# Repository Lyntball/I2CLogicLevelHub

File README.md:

# I2CLogicLevelHub
I2C Logic Level Hub for Sensor Reading and Device Control

This is a Logic Level Hub for Reading Sensors or controlling devices. Using the RJ-45 connections and normal network cabling devices can reach distances over 100 feet using onle I2C to communicate.

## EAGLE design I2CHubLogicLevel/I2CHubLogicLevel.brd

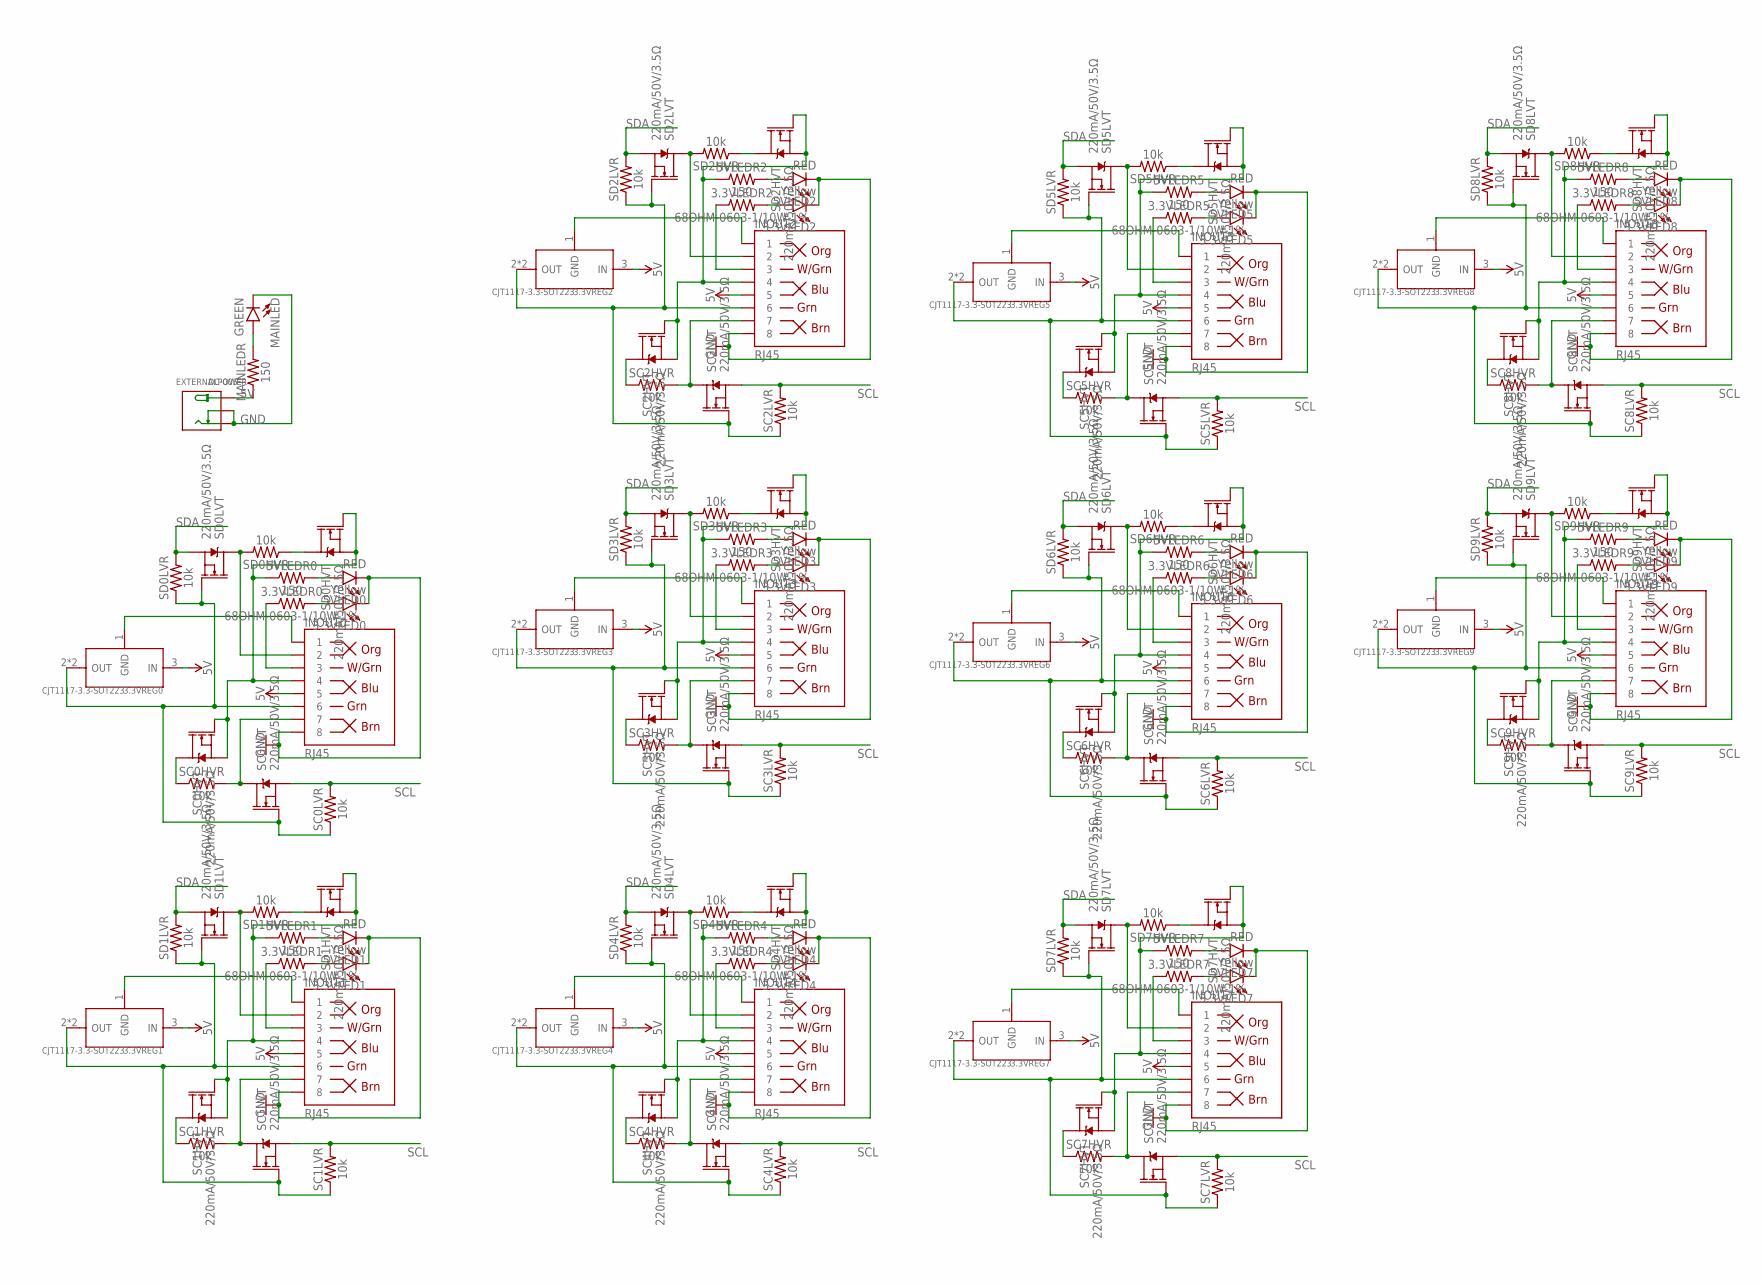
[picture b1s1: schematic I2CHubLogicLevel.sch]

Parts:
3.3VLED0, 3.3VLED1, 3.3VLED2, 3.3VLED3, 3.3VLED4, 3.3VLED5, 3.3VLED6, 3.3VLED7, 3.3VLED8, 3.3VLED9: Yellow; LED-0603
3.3VLEDR0, 3.3VLEDR1, 3.3VLEDR2, 3.3VLEDR3, 3.3VLEDR4, 3.3VLEDR5, 3.3VLEDR6, 3.3VLEDR7, 3.3VLEDR8, 3.3VLEDR9: 68OHM-0603-1/10W-1%; 0603
3.3VREG0, 3.3VREG1, 3.3VREG2, 3.3VREG3, 3.3VREG4, 3.3VREG5, 3.3VREG6, 3.3VREG7, 3.3VREG8, 3.3VREG9: CJT1117-3.3-SOT223; SOT-223
5VLED0, 5VLED1, 5VLED2, 5VLED3, 5VLED4, 5VLED5, 5VLED6, 5VLED7, 5VLED8, 5VLED9: RED; LED-0603
5VLEDR0, 5VLEDR1, 5VLEDR2, 5VLEDR3, 5VLEDR4, 5VLEDR5, 5VLEDR6, 5VLEDR7, 5VLEDR8, 5VLEDR9: 150; 0603
EXTERNALPOWER: DC-005; DCJ3P-14.2X11.0X9.0MM
INOUT0, INOUT1, INOUT2, INOUT3, INOUT4, INOUT5, INOUT6, INOUT7, INOUT8, INOUT9: RJ45; RJ45-8
MAINLED: GREEN; LED-0603
MAINLEDR: 150; 0603
SC0HVR, SC0LVR, SC1HVR, SC1LVR, SC2HVR, SC2LVR, SC3HVR, SC3LVR, SC4HVR, SC4LVR, SC5HVR, SC5LVR, SC6HVR, SC6LVR, SC7HVR, SC7LVR, SC8HVR, SC8LVR, SC9HVR, SC9LVR: 10k; 0603
SC0HVT, SC0LVT, SC1HVT, SC1LVT, SC2HVT, SC2LVT, SC3HVT, SC3LVT, SC4HVT, SC4LVT, SC5HVT, SC5LVT, SC6HVT, SC6LVT, SC7HVT, SC7LVT, SC8HVT, SC8LVT, SC9HVT, SC9LVT: 220mA/50V/3.5Ω; SOT23-3
SD0HVR, SD0LVR, SD1HVR, SD1LVR, SD2HVR, SD2LVR, SD3HVR, SD3LVR, SD4HVR, SD4LVR, SD5HVR, SD5LVR, SD6HVR, SD6LVR, SD7HVR, SD7LVR, SD8HVR, SD8LVR, SD9HVR, SD9LVR: 10k; 0603
SD0HVT, SD0LVT, SD1HVT, SD1LVT, SD2HVT, SD2LVT, SD3HVT, SD3LVT, SD4HVT, SD4LVT, SD5HVT, SD5LVT, SD6HVT, SD6LVT, SD7HVT, SD7LVT, SD8HVT, SD8LVT, SD9HVT, SD9LVT: 220mA/50V/3.5Ω; SOT23-3

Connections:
3.3CC0: 3.3VLEDR0.1, INOUT0.3
3.3CC1: 3.3VLEDR1.1, INOUT1.3
3.3CC2: 3.3VLEDR2.1, INOUT2.3
3.3CC3: 3.3VLEDR3.1, INOUT3.3
3.3CC4: 3.3VLEDR4.1, INOUT4.3
3.3CC5: 3.3VLEDR5.1, INOUT5.3
3.3CC6: 3.3VLEDR6.1, INOUT6.3
3.3CC7: 3.3VLEDR7.1, INOUT7.3
3.3CC8: 3.3VLEDR8.1, INOUT8.3
3.3CC9: 3.3VLEDR9.1, INOUT9.3
3.3LED0: 3.3VLED0.A, 3.3VLEDR0.2
3.3LED1: 3.3VLED1.A, 3.3VLEDR1.2
3.3LED2: 3.3VLED2.A, 3.3VLEDR2.2
3.3LED3: 3.3VLED3.A, 3.3VLEDR3.2
3.3LED4: 3.3VLED4.A, 3.3VLEDR4.2
3.3LED5: 3.3VLED5.A, 3.3VLEDR5.2
3.3LED6: 3.3VLED6.A, 3.3VLEDR6.2
3.3LED7: 3.3VLED7.A, 3.3VLEDR7.2
3.3LED8: 3.3VLED8.A, 3.3VLEDR8.2
3.3LED9: 3.3VLED9.A, 3.3VLEDR9.2
3.3V0: 3.3VREG0.2 (OUT), 3.3VREG0.TER (OUT), INOUT0.6, SC0LVR.1, SC0LVT.1 (G), SD0LVR.1, SD0LVT.1 (G)
3.3V1: 3.3VREG1.2 (OUT), 3.3VREG1.TER (OUT), INOUT1.6, SC1LVR.1, SC1LVT.1 (G), SD1LVR.1, SD1LVT.1 (G)
3.3V2: 3.3VREG2.2 (OUT), 3.3VREG2.TER (OUT), INOUT2.6, SC2LVR.1, SC2LVT.1 (G), SD2LVR.1, SD2LVT.1 (G)
3.3V3: 3.3VREG3.2 (OUT), 3.3VREG3.TER (OUT), INOUT3.6, SC3LVR.1, SC3LVT.1 (G), SD3LVR.1, SD3LVT.1 (G)
3.3V4: 3.3VREG4.2 (OUT), 3.3VREG4.TER (OUT), INOUT4.6, SC4LVR.1, SC4LVT.1 (G), SD4LVR.1, SD4LVT.1 (G)
3.3V5: 3.3VREG5.2 (OUT), 3.3VREG5.TER (OUT), INOUT5.6, SC5LVR.1, SC5LVT.1 (G), SD5LVR.1, SD5LVT.1 (G)
3.3V6: 3.3VREG6.2 (OUT), 3.3VREG6.TER (OUT), INOUT6.6, SC6LVR.1, SC6LVT.1 (G), SD6LVR.1, SD6LVT.1 (G)
3.3V7: 3.3VREG7.2 (OUT), 3.3VREG7.TER (OUT), INOUT7.6, SC7LVR.1, SC7LVT.1 (G), SD7LVR.1, SD7LVT.1 (G)
3.3V8: 3.3VREG8.2 (OUT), 3.3VREG8.TER (OUT), INOUT8.6, SC8LVR.1, SC8LVT.1 (G), SD8LVR.1, SD8LVT.1 (G)
3.3V9: 3.3VREG9.2 (OUT), 3.3VREG9.TER (OUT), INOUT9.6, SC9LVR.1, SC9LVT.1 (G), SD9LVR.1, SD9LVT.1 (G)
5V: 3.3VREG0.3 (IN), 3.3VREG1.3 (IN), 3.3VREG2.3 (IN), 3.3VREG3.3 (IN), 3.3VREG4.3 (IN), 3.3VREG5.3 (IN), 3.3VREG6.3 (IN), 3.3VREG7.3 (IN), 3.3VREG8.3 (IN), 3.3VREG9.3 (IN), EXTERNALPOWER.+, INOUT0.5, INOUT1.5, INOUT2.5, INOUT3.5, INOUT4.5, INOUT5.5, INOUT6.5, INOUT7.5, INOUT8.5, INOUT9.5, MAINLEDR.1
5VCC0: 5VLEDR0.1, INOUT0.4, SC0HVT.1 (G), SC0HVT.2 (S), SD0HVT.1 (G), SD0HVT.2 (S)
5VCC1: 5VLEDR1.1, INOUT1.4, SC1HVT.1 (G), SC1HVT.2 (S), SD1HVT.1 (G), SD1HVT.2 (S)
5VCC2: 5VLEDR2.1, INOUT2.4, SC2HVT.1 (G), SC2HVT.2 (S), SD2HVT.1 (G), SD2HVT.2 (S)
5VCC3: 5VLEDR3.1, INOUT3.4, SC3HVT.1 (G), SC3HVT.2 (S), SD3HVT.1 (G), SD3HVT.2 (S)
5VCC4: 5VLEDR4.1, INOUT4.4, SC4HVT.1 (G), SC4HVT.2 (S), SD4HVT.1 (G), SD4HVT.2 (S)
5VCC5: 5VLEDR5.1, INOUT5.4, SC5HVT.1 (G), SC5HVT.2 (S), SD5HVT.1 (G), SD5HVT.2 (S)
5VCC6: 5VLEDR6.1, INOUT6.4, SC6HVT.1 (G), SC6HVT.2 (S), SD6HVT.1 (G), SD6HVT.2 (S)
5VCC7: 5VLEDR7.1, INOUT7.4, SC7HVT.1 (G), SC7HVT.2 (S), SD7HVT.1 (G), SD7HVT.2 (S)
5VCC8: 5VLEDR8.1, INOUT8.4, SC8HVT.1 (G), SC8HVT.2 (S), SD8HVT.1 (G), SD8HVT.2 (S)
5VCC9: 5VLEDR9.1, INOUT9.4, SC9HVT.1 (G), SC9HVT.2 (S), SD9HVT.1 (G), SD9HVT.2 (S)
5VLED0: 5VLED0.A, 5VLEDR0.2
5VLED1: 5VLED1.A, 5VLEDR1.2
5VLED2: 5VLED2.A, 5VLEDR2.2
5VLED3: 5VLED3.A, 5VLEDR3.2
5VLED4: 5VLED4.A, 5VLEDR4.2
5VLED5: 5VLED5.A, 5VLEDR5.2
5VLED6: 5VLED6.A, 5VLEDR6.2
5VLED7: 5VLED7.A, 5VLEDR7.2
5VLED8: 5VLED8.A, 5VLEDR8.2
5VLED9: 5VLED9.A, 5VLEDR9.2
GND: 3.3VLED0.C, 3.3VLED1.C, 3.3VLED2.C, 3.3VLED3.C, 3.3VLED4.C, 3.3VLED5.C, 3.3VLED6.C, 3.3VLED7.C, 3.3VLED8.C, 3.3VLED9.C, 5VLED0.C, 5VLED1.C, 5VLED2.C, 5VLED3.C, 5VLED4.C, 5VLED5.C, 5VLED6.C, 5VLED7.C, 5VLED8.C, 5VLED9.C, EXTERNALPOWER.-1 (-), EXTERNALPOWER.-2 (CDN), INOUT0.8, INOUT1.8, INOUT2.8, INOUT3.8, INOUT4.8, INOUT5.8, INOUT6.8, INOUT7.8, INOUT8.8, INOUT9.8, MAINLED.C
GNDCC0: 3.3VREG0.1 (GND), INOUT0.1
GNDCC1: 3.3VREG1.1 (GND), INOUT1.1
GNDCC2: 3.3VREG2.1 (GND), INOUT2.1
GNDCC3: 3.3VREG3.1 (GND), INOUT3.1
GNDCC4: 3.3VREG4.1 (GND), INOUT4.1
GNDCC5: 3.3VREG5.1 (GND), INOUT5.1
GNDCC6: 3.3VREG6.1 (GND), INOUT6.1
GNDCC7: 3.3VREG7.1 (GND), INOUT7.1
GNDCC8: 3.3VREG8.1 (GND), INOUT8.1
GNDCC9: 3.3VREG9.1 (GND), INOUT9.1
MAINLED: MAINLED.A, MAINLEDR.2
SC0: INOUT0.7, SC0HVR.2, SC0LVT.3 (D)
SC1: INOUT1.7, SC1HVR.2, SC1LVT.3 (D)
SC2: INOUT2.7, SC2HVR.2, SC2LVT.3 (D)
SC3: INOUT3.7, SC3HVR.2, SC3LVT.3 (D)
SC4: INOUT4.7, SC4HVR.2, SC4LVT.3 (D)
SC5: INOUT5.7, SC5HVR.2, SC5LVT.3 (D)
SC6: INOUT6.7, SC6HVR.2, SC6LVT.3 (D)
SC7: INOUT7.7, SC7HVR.2, SC7LVT.3 (D)
SC8: INOUT8.7, SC8HVR.2, SC8LVT.3 (D)
SC9: INOUT9.7, SC9HVR.2, SC9LVT.3 (D)
SCHV0: SC0HVR.1, SC0HVT.3 (D)
SCHV1: SC1HVR.1, SC1HVT.3 (D)
SCHV2: SC2HVR.1, SC2HVT.3 (D)
SCHV3: SC3HVR.1, SC3HVT.3 (D)
SCHV4: SC4HVR.1, SC4HVT.3 (D)
SCHV5: SC5HVR.1, SC5HVT.3 (D)
SCHV6: SC6HVR.1, SC6HVT.3 (D)
SCHV7: SC7HVR.1, SC7HVT.3 (D)
SCHV8: SC8HVR.1, SC8HVT.3 (D)
SCHV9: SC9HVR.1, SC9HVT.3 (D)
SCL: SC0LVR.2, SC0LVT.2 (S), SC1LVR.2, SC1LVT.2 (S), SC2LVR.2, SC2LVT.2 (S), SC3LVR.2, SC3LVT.2 (S), SC4LVR.2, SC4LVT.2 (S), SC5LVR.2, SC5LVT.2 (S), SC6LVR.2, SC6LVT.2 (S), SC7LVR.2, SC7LVT.2 (S), SC8LVR.2, SC8LVT.2 (S), SC9LVR.2, SC9LVT.2 (S)
SD0: INOUT0.2, SD0HVR.2, SD0LVT.3 (D)
SD1: INOUT1.2, SD1HVR.2, SD1LVT.3 (D)
SD2: INOUT2.2, SD2HVR.2, SD2LVT.3 (D)
SD3: INOUT3.2, SD3HVR.2, SD3LVT.3 (D)
SD4: INOUT4.2, SD4HVR.2, SD4LVT.3 (D)
SD5: INOUT5.2, SD5HVR.2, SD5LVT.3 (D)
SD6: INOUT6.2, SD6HVR.2, SD6LVT.3 (D)
SD7: INOUT7.2, SD7HVR.2, SD7LVT.3 (D)
SD8: INOUT8.2, SD8HVR.2, SD8LVT.3 (D)
SD9: INOUT9.2, SD9HVR.2, SD9LVT.3 (D)
SDA: SD0LVR.2, SD0LVT.2 (S), SD1LVR.2, SD1LVT.2 (S), SD2LVR.2, SD2LVT.2 (S), SD3LVR.2, SD3LVT.2 (S), SD4LVR.2, SD4LVT.2 (S), SD5LVR.2, SD5LVT.2 (S), SD6LVR.2, SD6LVT.2 (S), SD7LVR.2, SD7LVT.2 (S), SD8LVR.2, SD8LVT.2 (S), SD9LVR.2, SD9LVT.2 (S)
SDHV0: SD0HVR.1, SD0HVT.3 (D)
SDHV1: SD1HVR.1, SD1HVT.3 (D)
SDHV2: SD2HVR.1, SD2HVT.3 (D)
SDHV3: SD3HVR.1, SD3HVT.3 (D)
SDHV4: SD4HVR.1, SD4HVT.3 (D)
SDHV5: SD5HVR.1, SD5HVT.3 (D)
SDHV6: SD6HVR.1, SD6HVT.3 (D)
SDHV7: SD7HVR.1, SD7HVT.3 (D)
SDHV8: SD8HVR.1, SD8HVT.3 (D)
SDHV9: SD9HVR.1, SD9HVT.3 (D)

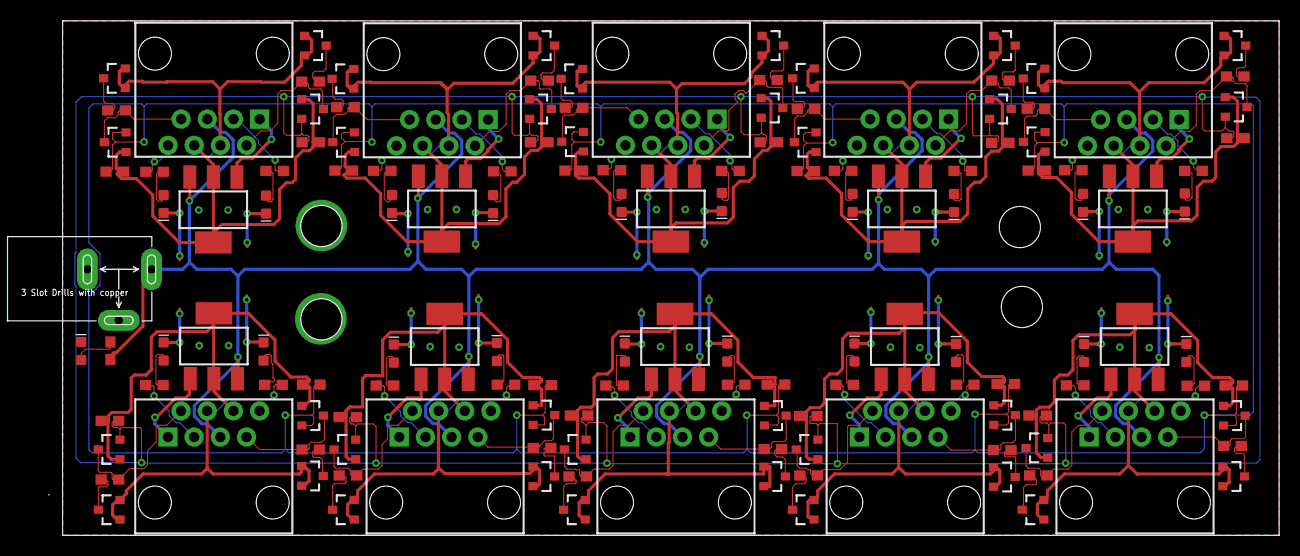
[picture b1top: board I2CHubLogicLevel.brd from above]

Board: 2 copper layers, 122.0 x 49.8 mm, 143 parts (0 on the bottom side), 105 nets.

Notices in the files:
parts and their libraries:
SparkFun-LED: Licensing: Creative Commons ShareAlike 4.0 International - https://creativecommons.org/licenses/by-sa/4.0
